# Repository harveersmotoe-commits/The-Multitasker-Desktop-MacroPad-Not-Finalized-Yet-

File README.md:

# The-Multitasker-Desktop-MacroPad
Macro Pad for Multitasking opportunities. Inspired by Blueprint HackPad but with 6 keys.

I thought of this idea due to the popular game on Roblox called Bee Swarm Simulator. And that I also love to take screenshots but everything I have to press 3 billion keys for it.

I have added STL files to this repo so that someone else can also follow along. PCB files are also located in the PCB folder. BOM is attached below. More details on how to build coming soon!
# Assembly (Prediction)

# PCB

# Schematics

*********************************************************************************************************
# BOM:

[HackPad BOM - Sheet1 (1).csv](https://github.com/user-attachments/files/23884668/HackPad.BOM.-.Sheet1.1.csv)

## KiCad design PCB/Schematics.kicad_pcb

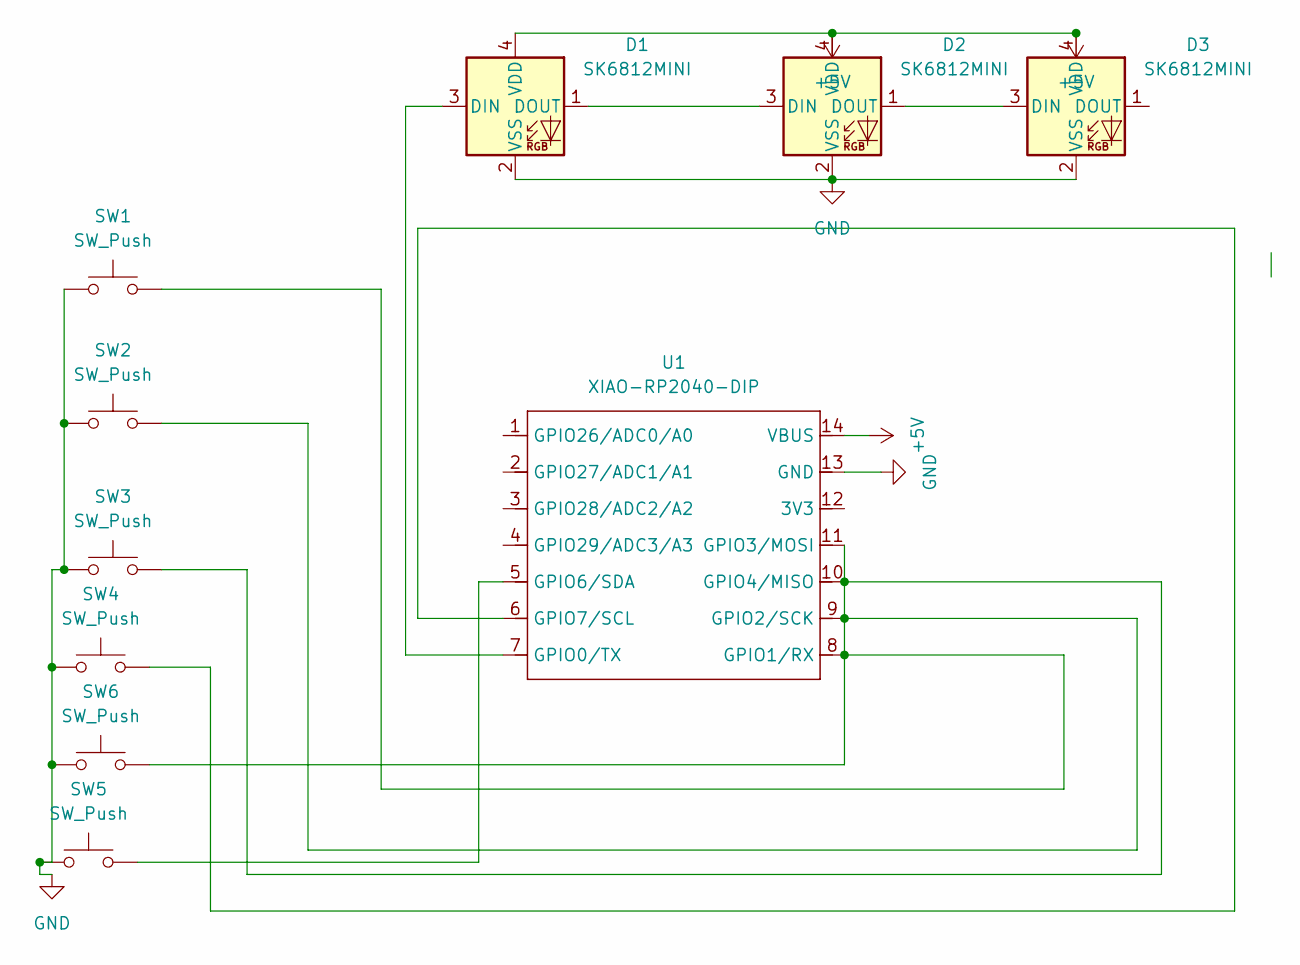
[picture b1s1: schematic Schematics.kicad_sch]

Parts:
D1, D2, D3: SK6812MINI; LED_SK6812MINI_PLCC4_3.5x3.5mm_P1.75mm
SW1, SW2, SW3, SW4, SW5, SW6: SW_Push; SW_Cherry_MX_1.00u_PCB
U1: XIAO-RP2040-DIP

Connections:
+5V: D1.4 (VDD), D2.4 (VDD), D3.4 (VDD), U1.14 (VBUS)
GND: D1.2 (VSS), D2.2 (VSS), D3.2 (VSS), SW1.1, SW2.1, SW3.1, SW4.1, SW5.1, SW6.1, U1.13 (GND)
unnamed: D1.3 (DIN), U1.7 (GPIO0/TX)
unnamed: D1.1 (DOUT), D2.3 (DIN)
unnamed: D2.1 (DOUT), D3.3 (DIN)
unnamed: SW1.2, SW2.2, SW3.2, SW6.2, U1.8 (GPIO1/RX), U1.9 (GPIO2/SCK), U1.10 (GPIO4/MISO), U1.11 (GPIO3/MOSI)
unnamed: SW5.2, U1.5 (GPIO6/SDA)
unnamed: SW4.2, U1.6 (GPIO7/SCL)

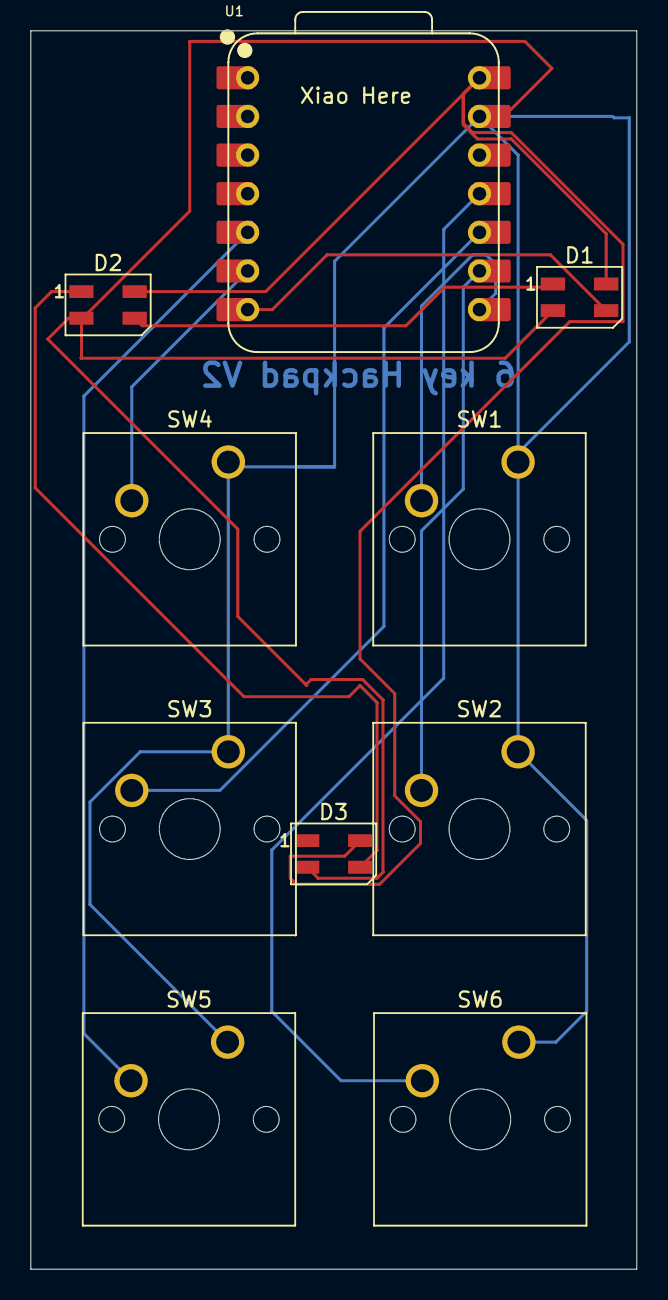
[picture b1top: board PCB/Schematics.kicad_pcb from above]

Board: 2 copper layers, 39.8 x 81.4 mm, 10 parts (0 on the bottom side), 8 nets.

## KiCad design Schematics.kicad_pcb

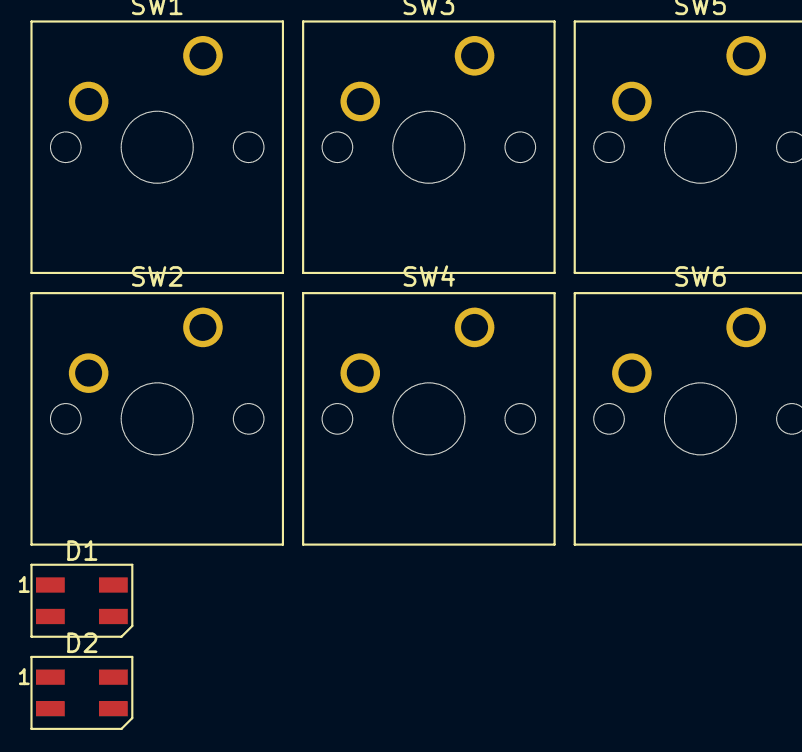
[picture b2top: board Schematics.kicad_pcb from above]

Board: 2 copper layers, 8 parts (0 on the bottom side), 3 nets, no tracks yet.

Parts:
D1, D2: SK6812MINI; LED_SK6812MINI_PLCC4_3.5x3.5mm_P1.75mm
SW1, SW2, SW3, SW4, SW5, SW6: SW_Push; SW_Cherry_MX_1.00u_PCB

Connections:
+5V: D1.4 (VDD), D2.4 (VDD)
GND: D1.2 (VSS), D2.2 (VSS), SW1.1, SW2.1, SW3.1, SW4.1, SW5.1, SW6.1
unnamed: D1.1 (DOUT), D2.3 (DIN)

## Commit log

2025-12-01 Add files via upload
    Added Updated Files of Schematics and PCB (Including PCB model)
2025-12-01 Update README.md
    Spacing Change
